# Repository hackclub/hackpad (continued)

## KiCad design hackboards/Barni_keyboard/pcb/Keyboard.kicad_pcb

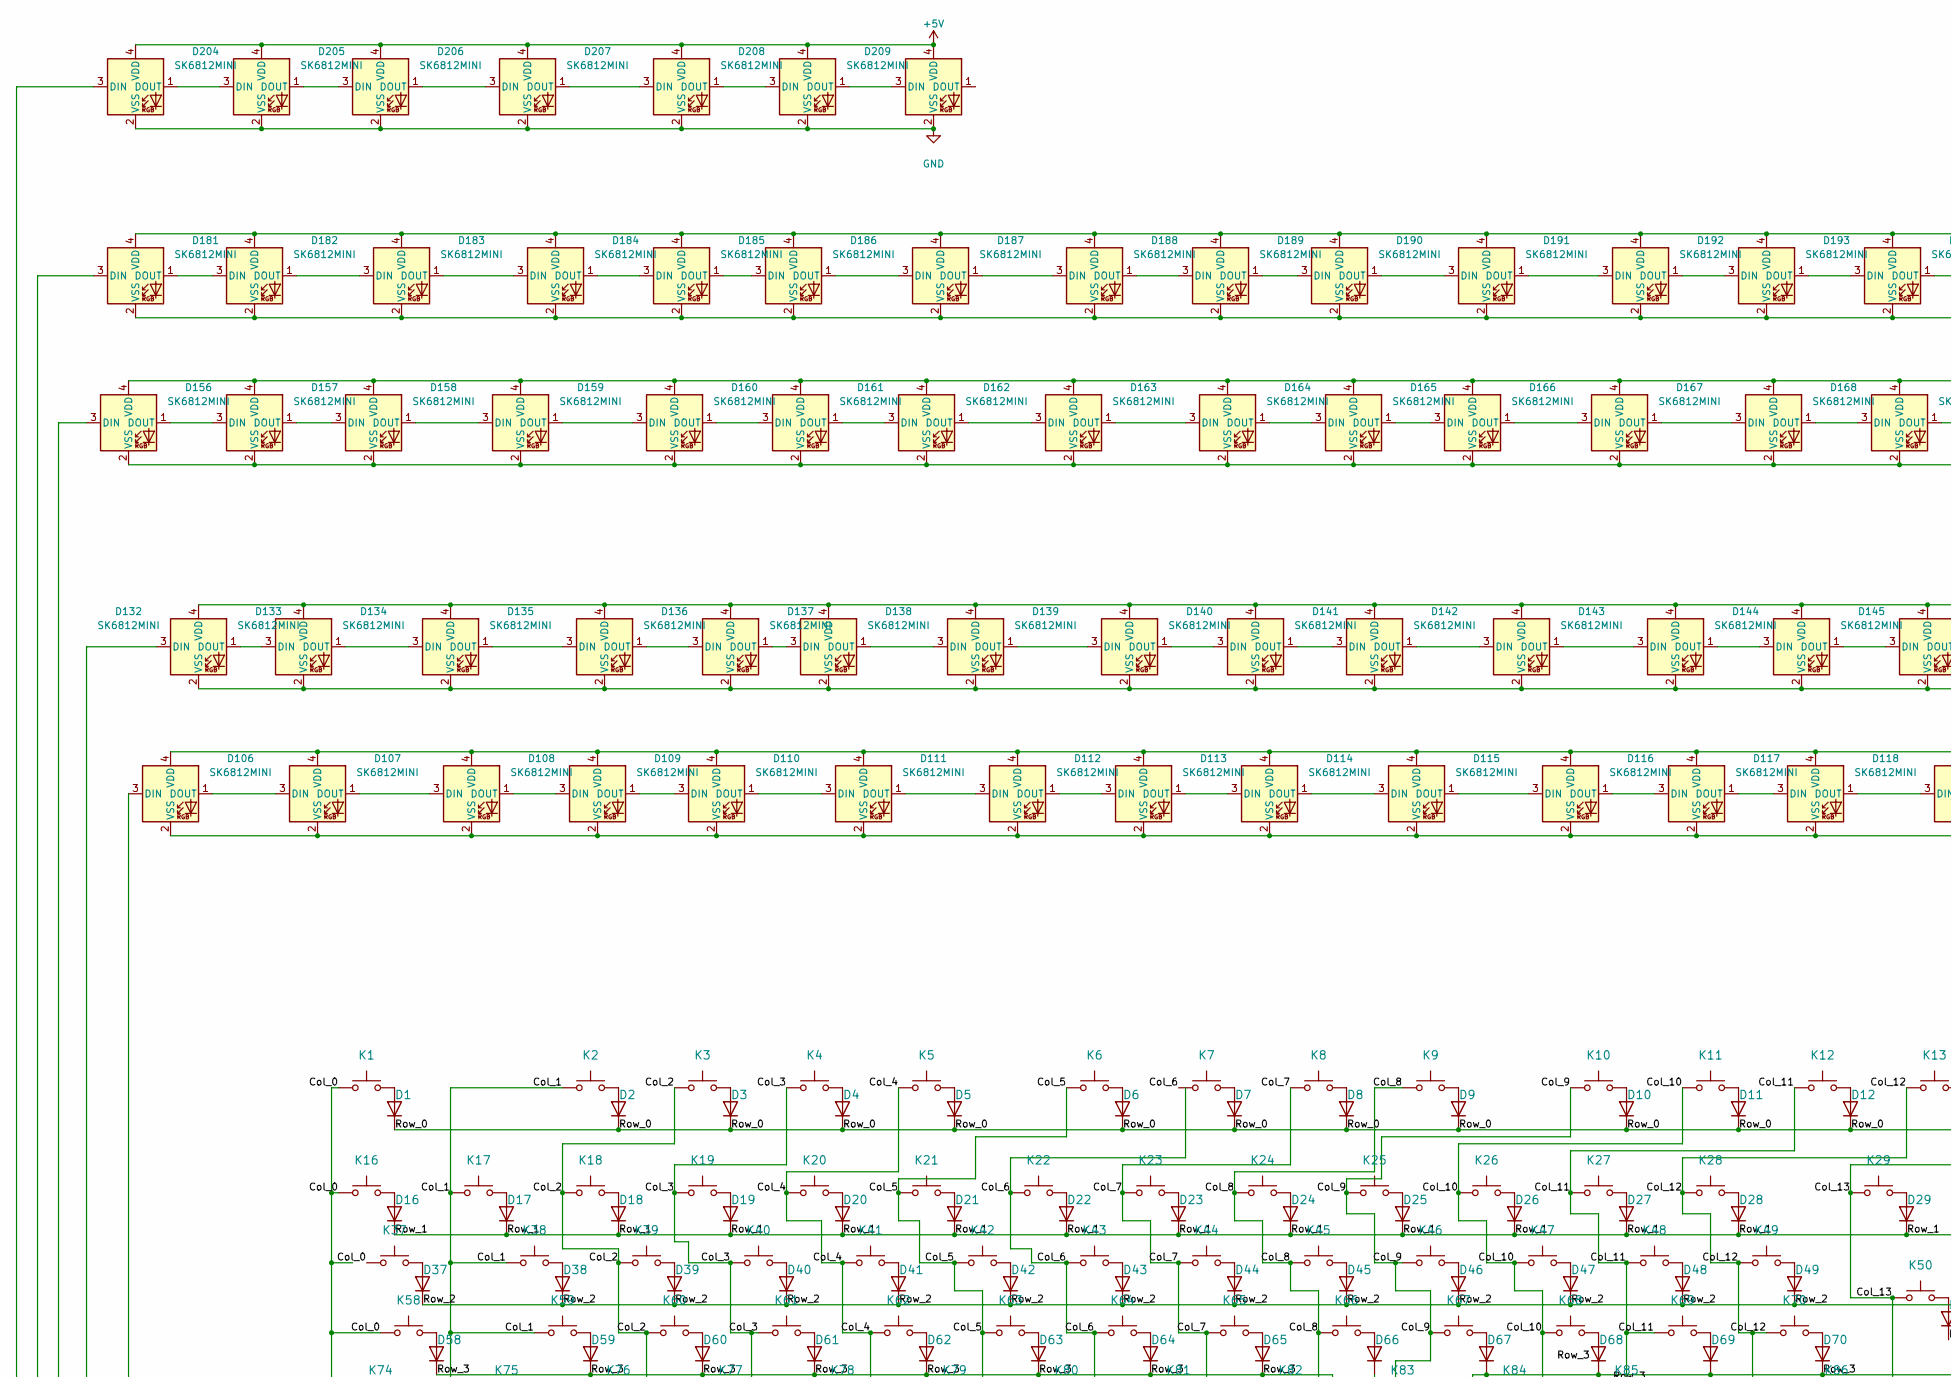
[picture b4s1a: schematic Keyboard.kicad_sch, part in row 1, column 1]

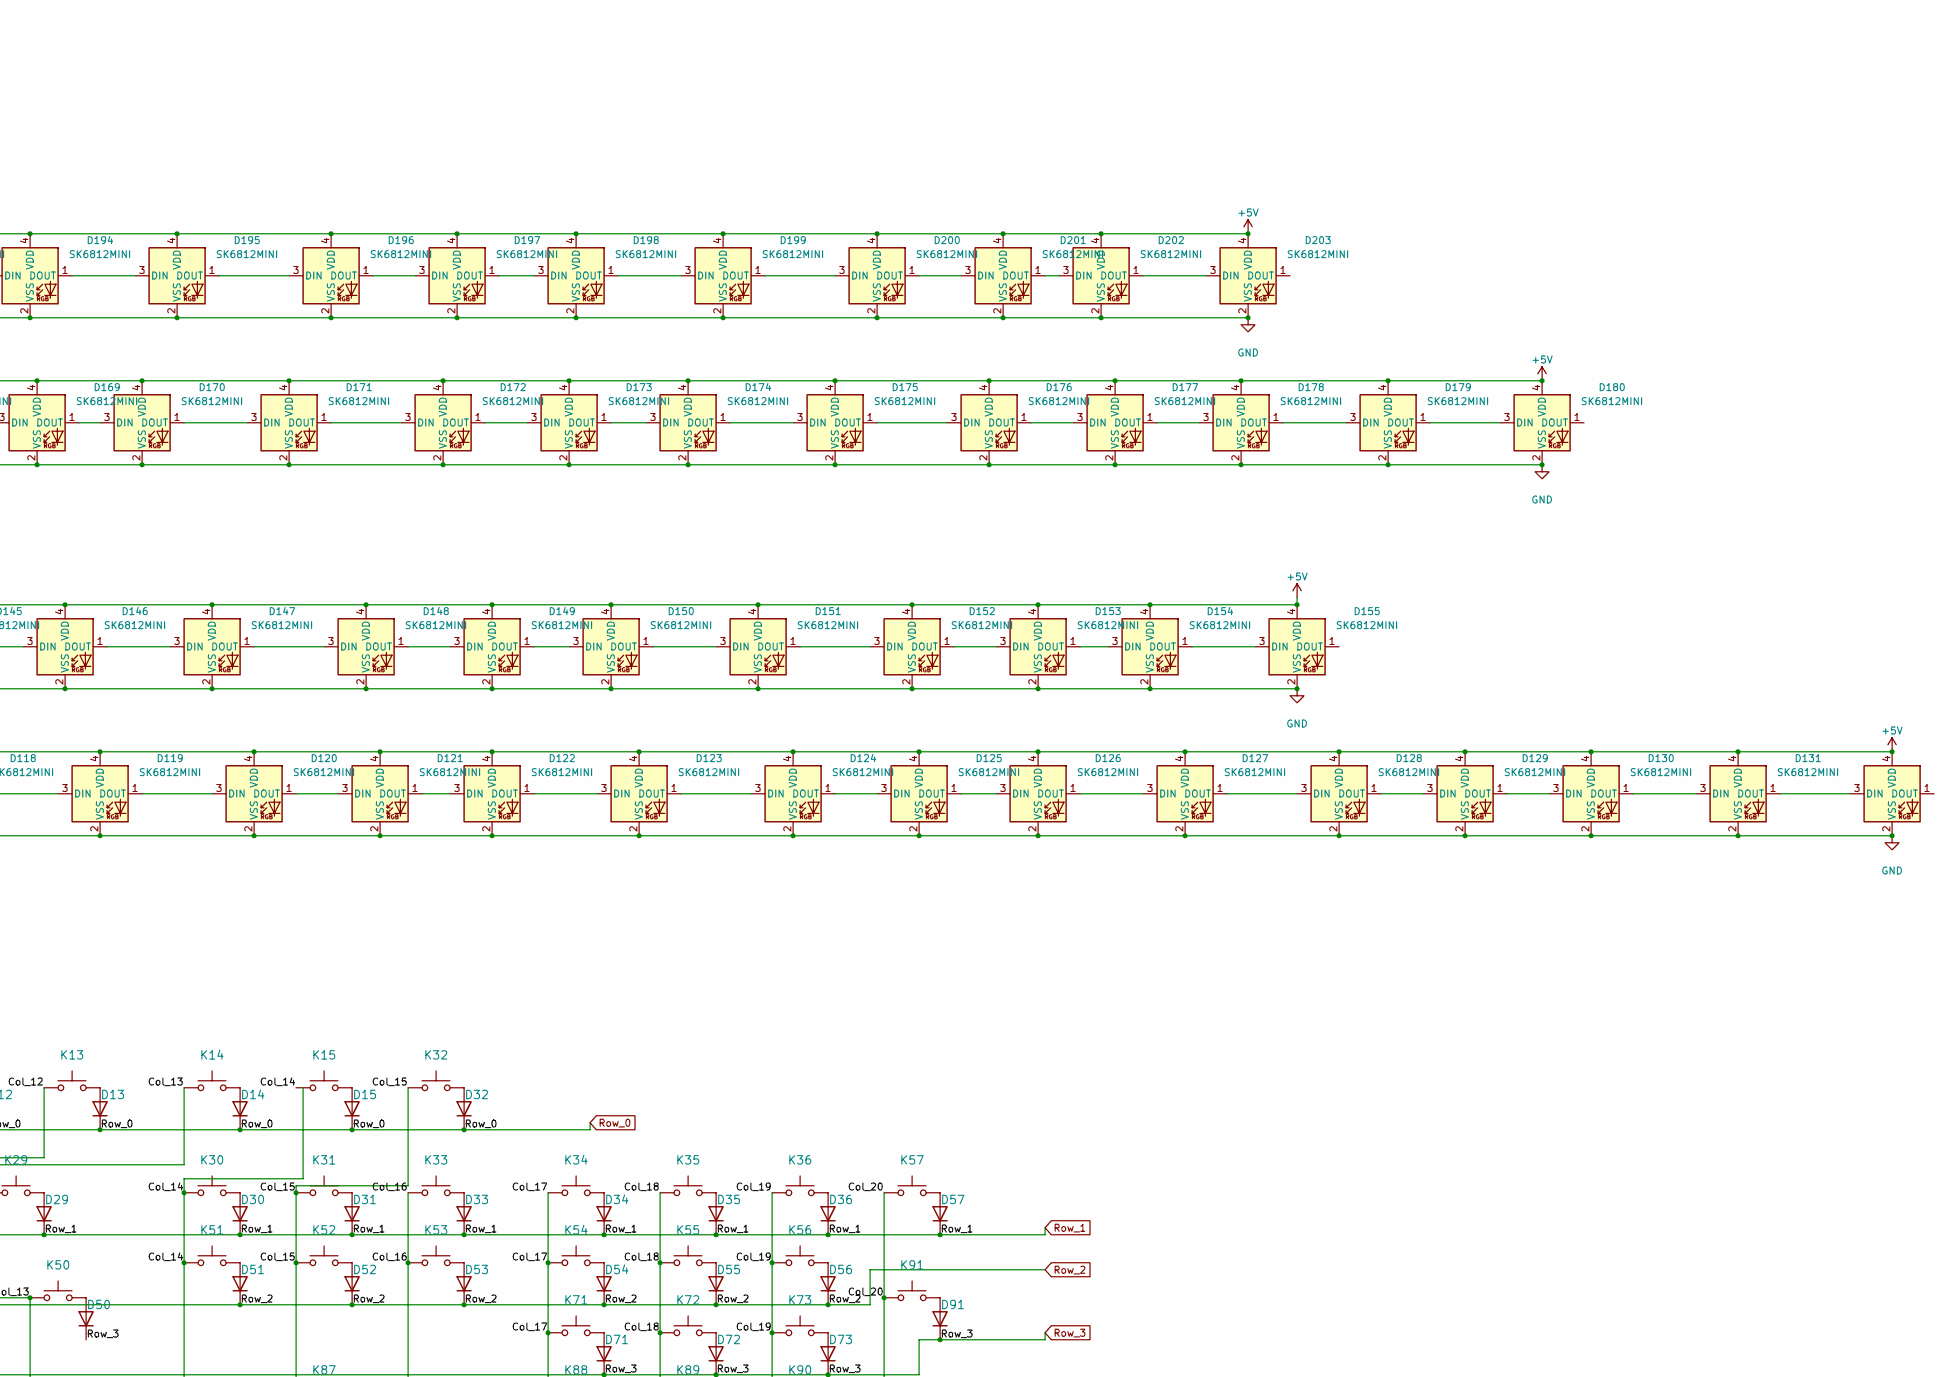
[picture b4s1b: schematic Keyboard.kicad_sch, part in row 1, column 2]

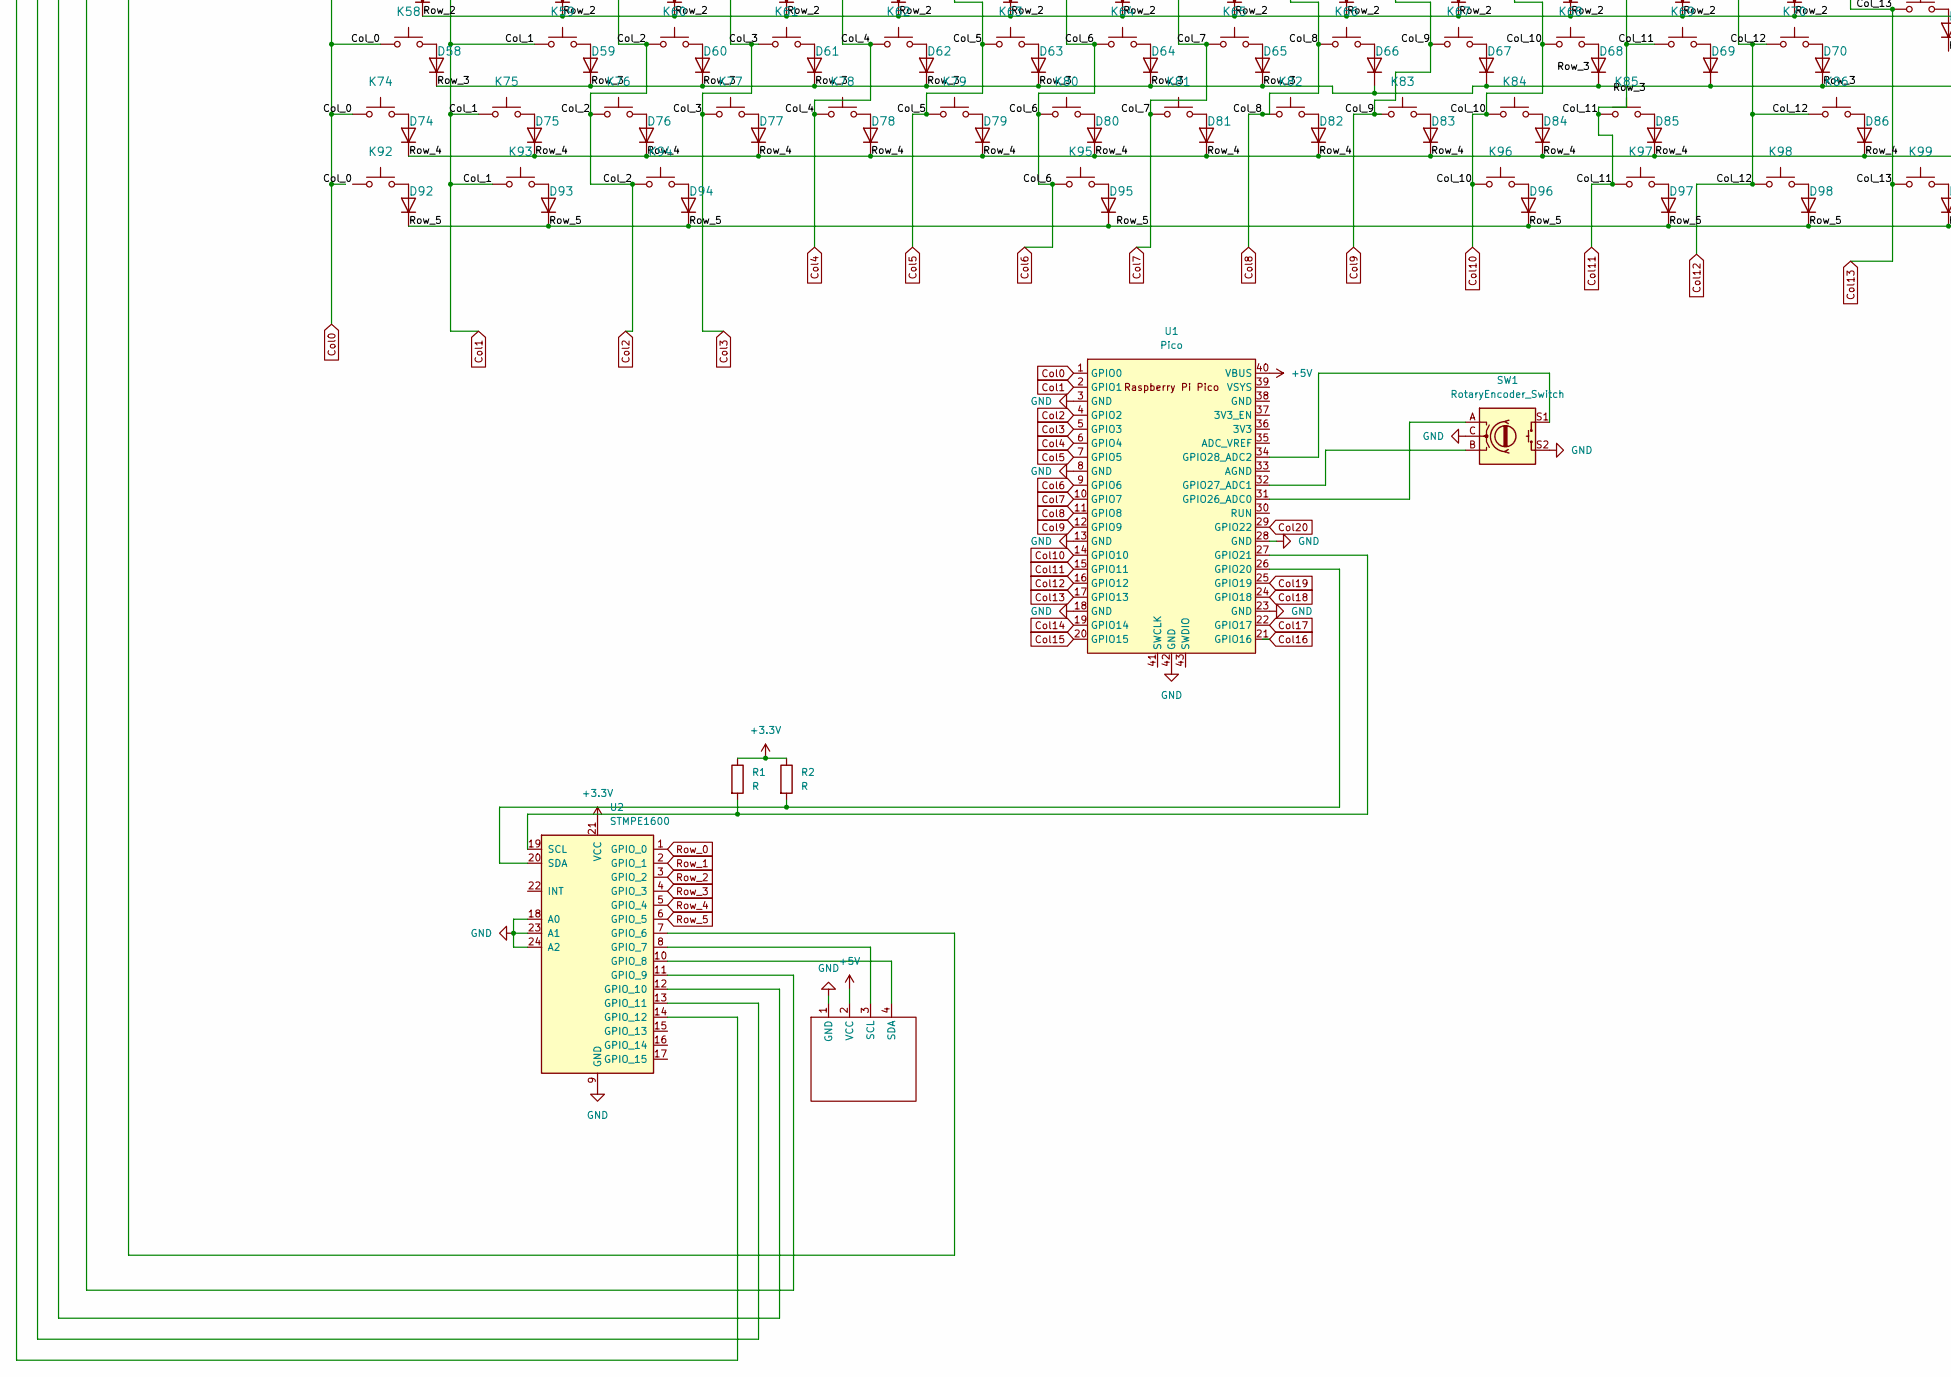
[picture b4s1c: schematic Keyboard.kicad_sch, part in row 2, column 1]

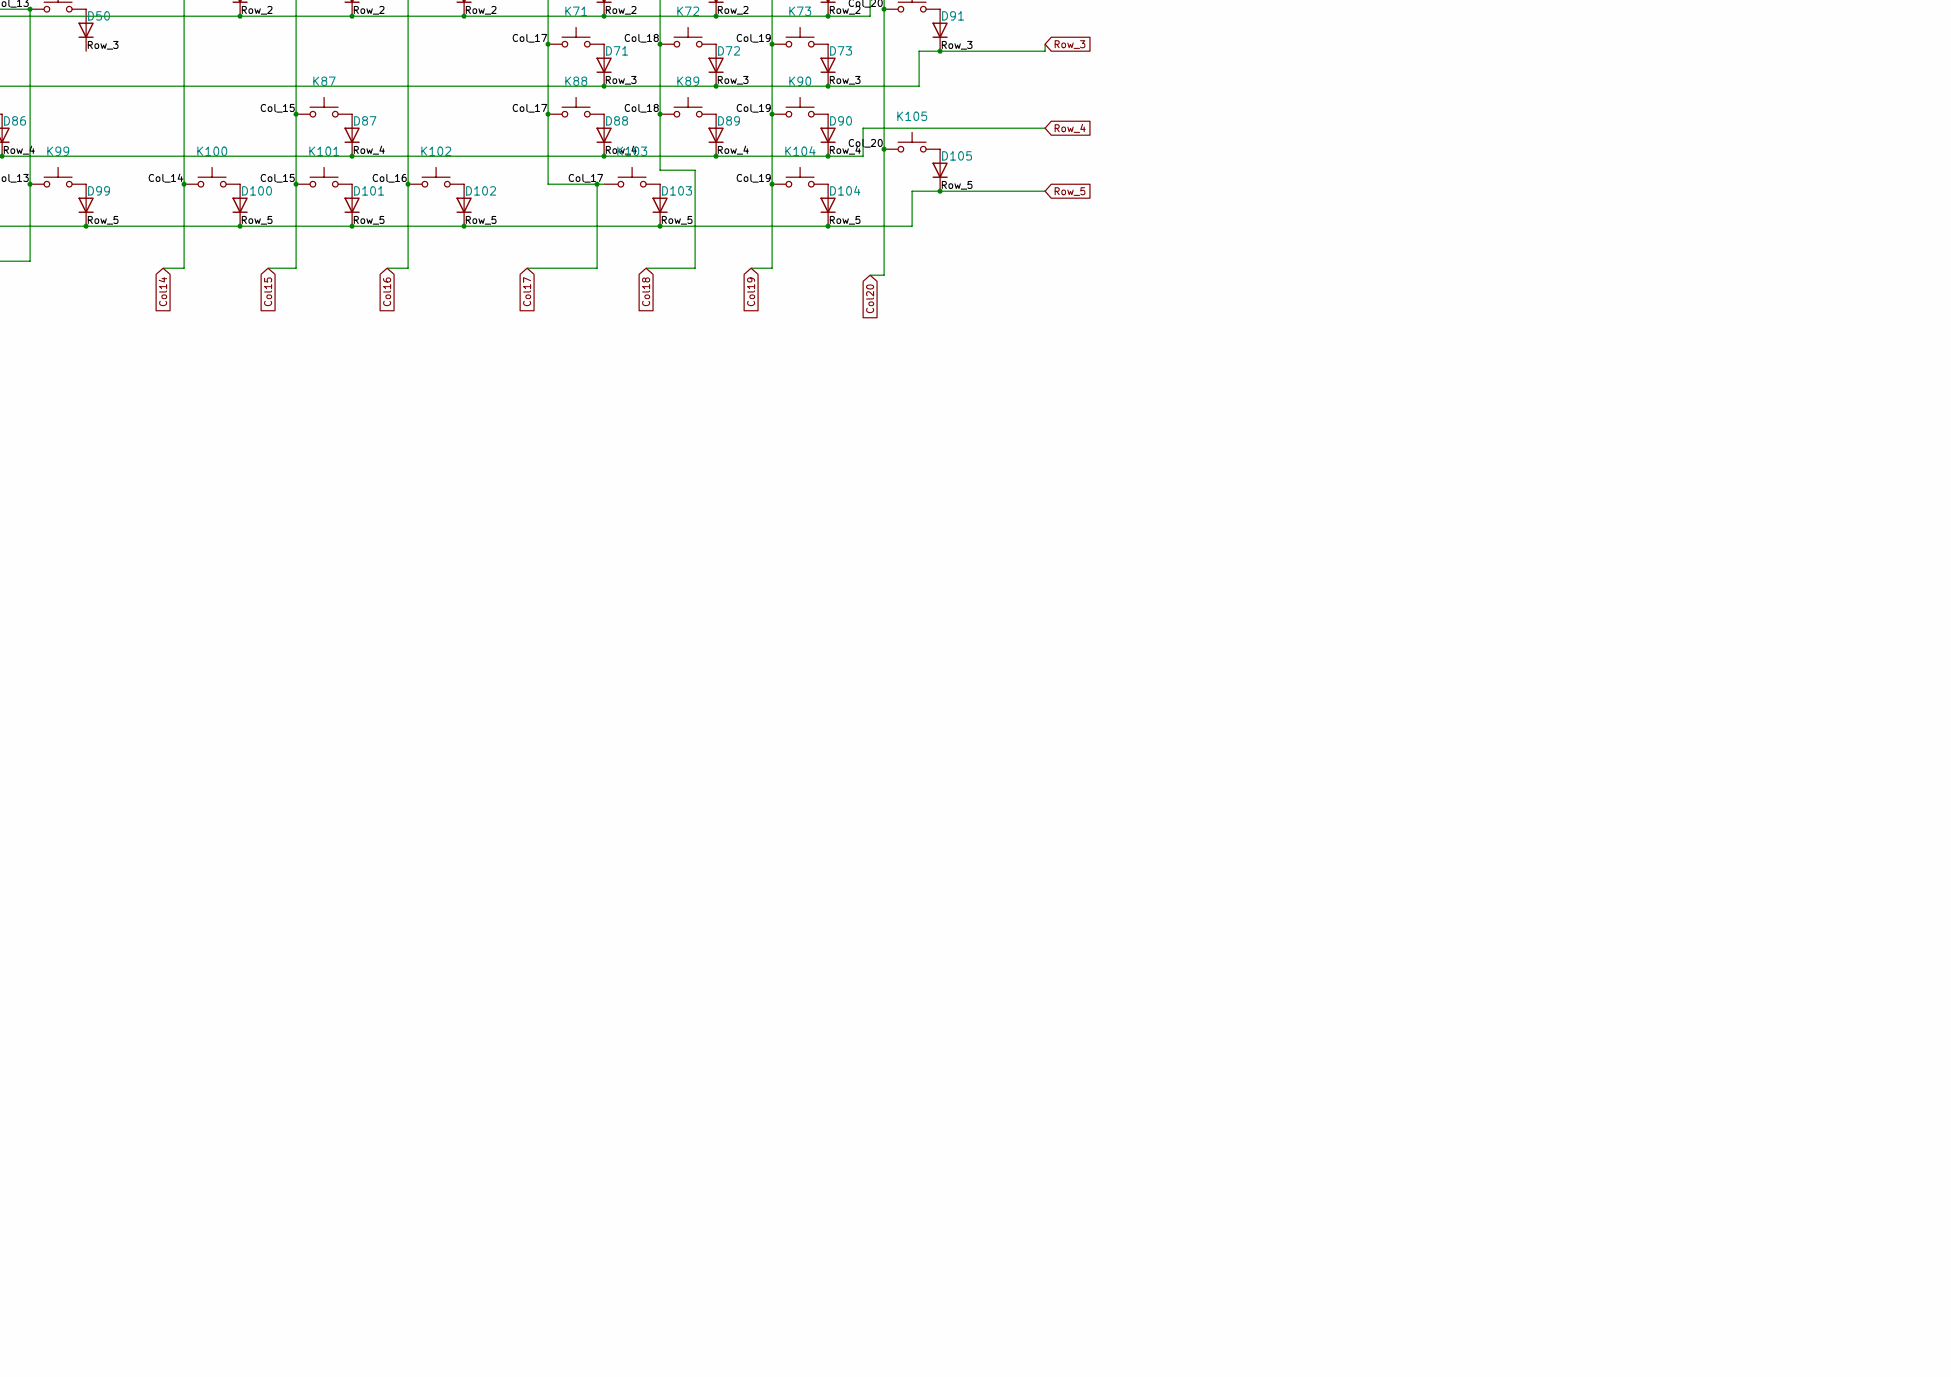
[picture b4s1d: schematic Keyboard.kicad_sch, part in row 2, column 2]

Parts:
D1, D2, D3, D4, D5, D6, D7, D8, D9, D10, D11, D12, D13, D14, D15, D16, D17, D18, D19, D20, D21, D22, D23, D24, D25, D26, D27, D28, D29, D30, D31, D32, D33, D34, D35, D36, D37, D38, D39, D40, D41, D42, D43, D44, D45, D46, D47, D48, D49, D50, D51, D52, D53, D54, D55, D56, D57, D58, D59, D60, D61, D62, D63, D64, D65, D66, D67, D68, D69, D70, D71, D72, D73, D74, D75, D76, D77, D78, D79, D80, D81, D82, D83, D84, D85, D86, D87, D88, D89, D90, D91, D92, D93, D94, D95, D96, D97, D98, D99, D100, D101, D102, D103, D104, D105: D; D_0805_2012Metric_Pad1.15x1.40mm_HandSolder
D106, D107, D108, D109, D110, D111, D112, D113, D114, D115, D116, D117, D118, D119, D120, D121, D122, D123, D124, D125, D126, D127, D128, D129, D130, D131, D132, D133, D134, D135, D136, D137, D138, D139, D140, D141, D142, D143, D144, D145, D146, D147, D148, D149, D150, D151, D152, D153, D154, D155, D156, D157, D158, D159, D160, D161, D162, D163, D164, D165, D166, D167, D168, D169, D170, D171, D172, D173, D174, D175, D176, D177, D178, D179, D180, D181, D182, D183, D184, D185, D186, D187, D188, D189, D190, D191, D192, D193, D194, D195, D196, D197, D198, D199, D200, D201, D202, D203, D204, D205, D206, D207, D208, D209, D210: SK6812MINI; LED_SK6812MINI_PLCC4_3.5x3.5mm_P1.75mm
K1: Esc; SW_Cherry_MX_1.00u_PCB
K2: F1; SW_Cherry_MX_1.00u_PCB
K3: F2; SW_Cherry_MX_1.00u_PCB
K4: F3; SW_Cherry_MX_1.00u_PCB
K5: F4; SW_Cherry_MX_1.00u_PCB
K6: F5; SW_Cherry_MX_1.00u_PCB
K7: F6; SW_Cherry_MX_1.00u_PCB
K8: F7; SW_Cherry_MX_1.00u_PCB
K9: F8; SW_Cherry_MX_1.00u_PCB
K10: F9; SW_Cherry_MX_1.00u_PCB
K11: F10; SW_Cherry_MX_1.00u_PCB
K12: F11; SW_Cherry_MX_1.00u_PCB
K13: F12; SW_Cherry_MX_1.00u_PCB
K14: PrtSc; SW_Cherry_MX_1.00u_PCB
K15: Scroll Lock; SW_Cherry_MX_1.00u_PCB
K16: ¬,`; SW_Cherry_MX_1.00u_PCB
K17: !,1; SW_Cherry_MX_1.00u_PCB
K18: ",2; SW_Cherry_MX_1.00u_PCB
K19: £,3; SW_Cherry_MX_1.00u_PCB
K20: $,4; SW_Cherry_MX_1.00u_PCB
K21: %,5; SW_Cherry_MX_1.00u_PCB
K22: ^,6; SW_Cherry_MX_1.00u_PCB
K23: &,7; SW_Cherry_MX_1.00u_PCB
K24: *,8; SW_Cherry_MX_1.00u_PCB
K25: (,9; SW_Cherry_MX_1.00u_PCB
K26: ),0; SW_Cherry_MX_1.00u_PCB
K27: _,-; SW_Cherry_MX_1.00u_PCB
K28: +,=; SW_Cherry_MX_1.00u_PCB
K29: Backspace; SW_Cherry_MX_2.00u_PCB
K30: Insert; SW_Cherry_MX_1.00u_PCB
K31: Home; SW_Cherry_MX_1.00u_PCB
K32: Pause,Break; SW_Cherry_MX_1.00u_PCB
K33: PgUp; SW_Cherry_MX_1.00u_PCB
K34: Num Lock; SW_Cherry_MX_1.00u_PCB
K35: /; SW_Cherry_MX_1.00u_PCB
K36: *; SW_Cherry_MX_1.00u_PCB
K37: Tab; SW_Cherry_MX_1.50u_PCB
K38: Q; SW_Cherry_MX_1.00u_PCB
K39: W; SW_Cherry_MX_1.00u_PCB
K40: E; SW_Cherry_MX_1.00u_PCB
K41: R; SW_Cherry_MX_1.00u_PCB
K42: T; SW_Cherry_MX_1.00u_PCB
K43: Y; SW_Cherry_MX_1.00u_PCB
K44: U; SW_Cherry_MX_1.00u_PCB
K45: I; SW_Cherry_MX_1.00u_PCB
K46: O; SW_Cherry_MX_1.00u_PCB
K47: P; SW_Cherry_MX_1.00u_PCB
K48: {,[; SW_Cherry_MX_1.00u_PCB
K49: },]; SW_Cherry_MX_1.00u_PCB
K50: Enter; SW_Cherry_MX_1.25u_PCB
K51: Delete; SW_Cherry_MX_1.00u_PCB
K52: End; SW_Cherry_MX_1.00u_PCB
K53: PgDn; SW_Cherry_MX_1.00u_PCB
K54: 7,Home; SW_Cherry_MX_1.00u_PCB
K55: 8,↑; SW_Cherry_MX_1.00u_PCB
K56: 9,PgUp; SW_Cherry_MX_1.00u_PCB
K57: -; SW_Cherry_MX_1.00u_PCB
K58: Caps Lock; SW_Cherry_MX_1.75u_PCB
K59: A; SW_Cherry_MX_1.00u_PCB
K60: S; SW_Cherry_MX_1.00u_PCB
K61: D; SW_Cherry_MX_1.00u_PCB
K62: F; SW_Cherry_MX_1.00u_PCB
K63: G; SW_Cherry_MX_1.00u_PCB
K64: H; SW_Cherry_MX_1.00u_PCB
K65: J; SW_Cherry_MX_1.00u_PCB
K66: K; SW_Cherry_MX_1.00u_PCB
K67: L; SW_Cherry_MX_1.00u_PCB
K68: :,;; SW_Cherry_MX_1.00u_PCB
K69: @,'; SW_Cherry_MX_1.00u_PCB
K70: ~~,#; SW_Cherry_MX_1.00u_PCB
K71: 4,←; SW_Cherry_MX_1.00u_PCB
K72: 5; SW_Cherry_MX_1.00u_PCB
K73: 6,→; SW_Cherry_MX_1.00u_PCB
K74: Shift; SW_Cherry_MX_1.25u_PCB
K75: |,\; SW_Cherry_MX_1.00u_PCB
K76: Z; SW_Cherry_MX_1.00u_PCB
K77: X; SW_Cherry_MX_1.00u_PCB
K78: C; SW_Cherry_MX_1.00u_PCB
K79: V; SW_Cherry_MX_1.00u_PCB
K80: B; SW_Cherry_MX_1.00u_PCB
K81: N; SW_Cherry_MX_1.00u_PCB
K82: M; SW_Cherry_MX_1.00u_PCB
K83: <,,; SW_Cherry_MX_1.00u_PCB
K84: >,.; SW_Cherry_MX_1.00u_PCB
K85: ?,/; SW_Cherry_MX_1.00u_PCB
K86: Shift; SW_Cherry_MX_2.75u_PCB
K87: ↑; SW_Cherry_MX_1.00u_PCB
K88: 1,End; SW_Cherry_MX_1.00u_PCB
K89: 2,↓; SW_Cherry_MX_1.00u_PCB
K90: 3,PgDn; SW_Cherry_MX_1.00u_PCB
K91: +; SW_Cherry_MX_1.00u_PCB
K92, K99: Ctrl; SW_Cherry_MX_1.25u_PCB
K93, K97: Win; SW_Cherry_MX_1.25u_PCB
K94: Alt; SW_Cherry_MX_1.25u_PCB
K95: Blank; SW_Cherry_MX_6.25u_PCB
K96: AltGr; SW_Cherry_MX_1.25u_PCB
K98: Menu; SW_Cherry_MX_1.25u_PCB
K100: ←; SW_Cherry_MX_1.00u_PCB
K101: ↓; SW_Cherry_MX_1.00u_PCB
K102: →; SW_Cherry_MX_1.00u_PCB
K103: 0,Ins; SW_Cherry_MX_2.00u_PCB
K104: .,Del; SW_Cherry_MX_1.00u_PCB
K105: Enter; SW_Cherry_MX_1.00u_PCB
R1, R2: R; R_Axial_DIN0204_L3.6mm_D1.6mm_P7.62mm_Horizontal
SW1: RotaryEncoder_Switch; RotaryEncoder_Alps_EC11E-Switch_Vertical_H20mm
U1: Pico; RPi_Pico_SMD_TH
U2: STMPE1600; 16-bit IO Expander
U3: (no value)

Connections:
+3.3V: R1.1, R2.1, U2.21 (VCC)
+5V: D106.4 (VDD), D107.4 (VDD), D108.4 (VDD), D109.4 (VDD), D110.4 (VDD), D111.4 (VDD), D112.4 (VDD), D113.4 (VDD), D114.4 (VDD), D115.4 (VDD), D116.4 (VDD), D117.4 (VDD), D118.4 (VDD), D119.4 (VDD), D120.4 (VDD), D121.4 (VDD), D122.4 (VDD), D123.4 (VDD), D124.4 (VDD), D125.4 (VDD), D126.4 (VDD), D127.4 (VDD), D128.4 (VDD), D129.4 (VDD), D130.4 (VDD), D131.4 (VDD), D132.4 (VDD), D133.4 (VDD), D134.4 (VDD), D135.4 (VDD), D136.4 (VDD), D137.4 (VDD), D138.4 (VDD), D139.4 (VDD), D140.4 (VDD), D141.4 (VDD), D142.4 (VDD), D143.4 (VDD), D144.4 (VDD), D145.4 (VDD), D146.4 (VDD), D147.4 (VDD), D148.4 (VDD), D149.4 (VDD), D150.4 (VDD), D151.4 (VDD), D152.4 (VDD), D153.4 (VDD), D154.4 (VDD), D155.4 (VDD), D156.4 (VDD), D157.4 (VDD), D158.4 (VDD), D159.4 (VDD), D160.4 (VDD), D161.4 (VDD), D162.4 (VDD), D163.4 (VDD), D164.4 (VDD), D165.4 (VDD), D166.4 (VDD), D167.4 (VDD), D168.4 (VDD), D169.4 (VDD), D170.4 (VDD), D171.4 (VDD), D172.4 (VDD), D173.4 (VDD), D174.4 (VDD), D175.4 (VDD), D176.4 (VDD), D177.4 (VDD), D178.4 (VDD), D179.4 (VDD), D180.4 (VDD), D181.4 (VDD), D182.4 (VDD), D183.4 (VDD), D184.4 (VDD), D185.4 (VDD), D186.4 (VDD), D187.4 (VDD), D188.4 (VDD), D189.4 (VDD), D190.4 (VDD), D191.4 (VDD), D192.4 (VDD), D193.4 (VDD), D194.4 (VDD), D195.4 (VDD), D196.4 (VDD), D197.4 (VDD), D198.4 (VDD), D199.4 (VDD), D200.4 (VDD), D201.4 (VDD), D202.4 (VDD), D203.4 (VDD), D204.4 (VDD), D205.4 (VDD), D206.4 (VDD), D207.4 (VDD), D208.4 (VDD), D209.4 (VDD), D210.4 (VDD), U1.40 (VBUS), U3.2 (VCC)
Col0: K1.1, K16.1, K37.1, K58.1, K74.1, K92.1, U1.1 (GPIO0)
Col1: K2.1, K17.1, K38.1, K59.1, K75.1, K93.1, U1.2 (GPIO1)
Col2: K3.1, K18.1, K39.1, K60.1, K76.1, K94.1, U1.4 (GPIO2)
Col3: K4.1, K19.1, K40.1, K61.1, K77.1, U1.5 (GPIO3)
Col4: K5.1, K20.1, K41.1, K62.1, K78.1, U1.6 (GPIO4)
Col5: K6.1, K21.1, K42.1, K63.1, K79.1, U1.7 (GPIO5)
Col6: K7.1, K22.1, K43.1, K64.1, K80.1, K95.1, U1.9 (GPIO6)
Col7: K8.1, K23.1, K44.1, K65.1, K81.1, U1.10 (GPIO7)
Col8: K9.1, K24.1, K45.1, K66.1, K82.1, U1.11 (GPIO8)
Col9: K10.1, K25.1, K46.1, K67.1, K83.1, U1.12 (GPIO9)
Col10: K11.1, K26.1, K47.1, K68.1, K84.1, K96.1, U1.14 (GPIO10)
Col11: K12.1, K27.1, K48.1, K69.1, K85.1, K97.1, U1.15 (GPIO11)
Col12: K13.1, K28.1, K49.1, K70.1, K86.1, K98.1, U1.16 (GPIO12)
Col13: K14.1, K29.1, K50.1, K99.1, U1.17 (GPIO13)
Col14: K15.1, K30.1, K51.1, K100.1, U1.19 (GPIO14)
Col15: K31.1, K32.1, K52.1, K87.1, K101.1, U1.20 (GPIO15)
Col16: K33.1, K53.1, K102.1, U1.21 (GPIO16)
Col17: K34.1, K54.1, K71.1, K88.1, K103.1, U1.22 (GPIO17)
Col18: K35.1, K55.1, K72.1, K89.1, U1.24 (GPIO18)
Col19: K36.1, K56.1, K73.1, K90.1, K104.1, U1.25 (GPIO19)
Col20: K57.1, K91.1, K105.1, U1.29 (GPIO22)
GND: D106.2 (VSS), D107.2 (VSS), D108.2 (VSS), D109.2 (VSS), D110.2 (VSS), D111.2 (VSS), D112.2 (VSS), D113.2 (VSS), D114.2 (VSS), D115.2 (VSS), D116.2 (VSS), D117.2 (VSS), D118.2 (VSS), D119.2 (VSS), D120.2 (VSS), D121.2 (VSS), D122.2 (VSS), D123.2 (VSS), D124.2 (VSS), D125.2 (VSS), D126.2 (VSS), D127.2 (VSS), D128.2 (VSS), D129.2 (VSS), D130.2 (VSS), D131.2 (VSS), D132.2 (VSS), D133.2 (VSS), D134.2 (VSS), D135.2 (VSS), D136.2 (VSS), D137.2 (VSS), D138.2 (VSS), D139.2 (VSS), D140.2 (VSS), D141.2 (VSS), D142.2 (VSS), D143.2 (VSS), D144.2 (VSS), D145.2 (VSS), D146.2 (VSS), D147.2 (VSS), D148.2 (VSS), D149.2 (VSS), D150.2 (VSS), D151.2 (VSS), D152.2 (VSS), D153.2 (VSS), D154.2 (VSS), D155.2 (VSS), D156.2 (VSS), D157.2 (VSS), D158.2 (VSS), D159.2 (VSS), D160.2 (VSS), D161.2 (VSS), D162.2 (VSS), D163.2 (VSS), D164.2 (VSS), D165.2 (VSS), D166.2 (VSS), D167.2 (VSS), D168.2 (VSS), D169.2 (VSS), D170.2 (VSS), D171.2 (VSS), D172.2 (VSS), D173.2 (VSS), D174.2 (VSS), D175.2 (VSS), D176.2 (VSS), D177.2 (VSS), D178.2 (VSS), D179.2 (VSS), D180.2 (VSS), D181.2 (VSS), D182.2 (VSS), D183.2 (VSS), D184.2 (VSS), D185.2 (VSS), D186.2 (VSS), D187.2 (VSS), D188.2 (VSS), D189.2 (VSS), D190.2 (VSS), D191.2 (VSS), D192.2 (VSS), D193.2 (VSS), D194.2 (VSS), D195.2 (VSS), D196.2 (VSS), D197.2 (VSS), D198.2 (VSS), D199.2 (VSS), D200.2 (VSS), D201.2 (VSS), D202.2 (VSS), D203.2 (VSS), D204.2 (VSS), D205.2 (VSS), D206.2 (VSS), D207.2 (VSS), D208.2 (VSS), D209.2 (VSS), D210.2 (VSS), SW1.C, SW1.S2, U1.3 (GND), U1.8 (GND), U1.13 (GND), U1.18 (GND), U1.23 (GND), U1.28 (GND), U1.42 (GND), U2.9 (GND), U2.18 (A0), U2.23 (A1), U2.24 (A2), U3.1 (GND)
unnamed: D1.2 (A), K1.2
unnamed: D2.2 (A), K2.2
unnamed: D3.2 (A), K3.2
unnamed: D4.2 (A), K4.2
unnamed: D5.2 (A), K5.2
unnamed: D6.2 (A), K6.2
unnamed: D7.2 (A), K7.2
unnamed: D8.2 (A), K8.2
unnamed: D9.2 (A), K9.2
unnamed: D10.2 (A), K10.2
unnamed: D11.2 (A), K11.2
unnamed: D12.2 (A), K12.2
unnamed: D13.2 (A), K13.2
unnamed: D14.2 (A), K14.2
unnamed: D15.2 (A), K15.2
unnamed: D16.2 (A), K16.2
unnamed: D17.2 (A), K17.2
unnamed: D18.2 (A), K18.2
unnamed: D19.2 (A), K19.2
unnamed: D20.2 (A), K20.2
unnamed: D21.2 (A), K21.2
unnamed: D22.2 (A), K22.2
unnamed: D23.2 (A), K23.2
unnamed: D24.2 (A), K24.2
unnamed: D25.2 (A), K25.2
unnamed: D26.2 (A), K26.2
unnamed: D27.2 (A), K27.2
unnamed: D28.2 (A), K28.2
unnamed: D29.2 (A), K29.2
unnamed: D30.2 (A), K30.2
unnamed: D31.2 (A), K31.2
unnamed: D32.2 (A), K32.2
unnamed: D33.2 (A), K33.2
unnamed: D34.2 (A), K34.2
unnamed: D35.2 (A), K35.2
unnamed: D36.2 (A), K36.2
unnamed: D37.2 (A), K37.2
unnamed: D38.2 (A), K38.2
unnamed: D39.2 (A), K39.2
unnamed: D40.2 (A), K40.2
unnamed: D41.2 (A), K41.2
unnamed: D42.2 (A), K42.2
unnamed: D43.2 (A), K43.2
unnamed: D44.2 (A), K44.2
unnamed: D45.2 (A), K45.2
unnamed: D46.2 (A), K46.2
unnamed: D47.2 (A), K47.2
unnamed: D48.2 (A), K48.2
unnamed: D49.2 (A), K49.2
unnamed: D50.2 (A), K50.2
unnamed: D51.2 (A), K51.2
unnamed: D52.2 (A), K52.2
unnamed: D53.2 (A), K53.2
unnamed: D54.2 (A), K54.2
unnamed: D55.2 (A), K55.2
unnamed: D56.2 (A), K56.2
unnamed: D57.2 (A), K57.2
unnamed: D58.2 (A), K58.2
unnamed: D59.2 (A), K59.2
unnamed: D60.2 (A), K60.2
unnamed: D61.2 (A), K61.2
unnamed: D62.2 (A), K62.2
unnamed: D63.2 (A), K63.2
unnamed: D64.2 (A), K64.2
unnamed: D65.2 (A), K65.2
unnamed: D66.2 (A), K66.2
unnamed: D67.2 (A), K67.2
unnamed: D68.2 (A), K68.2
unnamed: D69.2 (A), K69.2
unnamed: D70.2 (A), K70.2
unnamed: D71.2 (A), K71.2
unnamed: D72.2 (A), K72.2
unnamed: D73.2 (A), K73.2
unnamed: D74.2 (A), K74.2
unnamed: D75.2 (A), K75.2
unnamed: D76.2 (A), K76.2
unnamed: D77.2 (A), K77.2
unnamed: D78.2 (A), K78.2
unnamed: D79.2 (A), K79.2
unnamed: D80.2 (A), K80.2
unnamed: D81.2 (A), K81.2
unnamed: D82.2 (A), K82.2
unnamed: D83.2 (A), K83.2
unnamed: D84.2 (A), K84.2
unnamed: D85.2 (A), K85.2
unnamed: D86.2 (A), K86.2
unnamed: D87.2 (A), K87.2
unnamed: D88.2 (A), K88.2
unnamed: D89.2 (A), K89.2
unnamed: D90.2 (A), K90.2
unnamed: D91.2 (A), K91.2
unnamed: D92.2 (A), K92.2
unnamed: D93.2 (A), K93.2
unnamed: D94.2 (A), K94.2
unnamed: D95.2 (A), K95.2
unnamed: D96.2 (A), K96.2
unnamed: D97.2 (A), K97.2
unnamed: D98.2 (A), K98.2
unnamed: D99.2 (A), K99.2
unnamed: D100.2 (A), K100.2
unnamed: D101.2 (A), K101.2
unnamed: D102.2 (A), K102.2
unnamed: D103.2 (A), K103.2
unnamed: D104.2 (A), K104.2
unnamed: D105.2 (A), K105.2
unnamed: D106.3 (DIN), U2.7 (GPIO_6)
unnamed: D106.1 (DOUT), D107.3 (DIN)
unnamed: D107.1 (DOUT), D108.3 (DIN)
unnamed: D108.1 (DOUT), D109.3 (DIN)
unnamed: D109.1 (DOUT), D110.3 (DIN)
unnamed: D110.1 (DOUT), D111.3 (DIN)
unnamed: D111.1 (DOUT), D112.3 (DIN)
unnamed: D112.1 (DOUT), D113.3 (DIN)
unnamed: D113.1 (DOUT), D114.3 (DIN)
unnamed: D114.1 (DOUT), D115.3 (DIN)
unnamed: D115.1 (DOUT), D116.3 (DIN)
unnamed: D116.1 (DOUT), D117.3 (DIN)
unnamed: D117.1 (DOUT), D118.3 (DIN)
unnamed: D118.1 (DOUT), D119.3 (DIN)
unnamed: D119.1 (DOUT), D120.3 (DIN)
unnamed: D120.1 (DOUT), D121.3 (DIN)
unnamed: D121.1 (DOUT), D122.3 (DIN)
unnamed: D122.1 (DOUT), D123.3 (DIN)
unnamed: D123.1 (DOUT), D124.3 (DIN)
unnamed: D124.1 (DOUT), D125.3 (DIN)
unnamed: D125.1 (DOUT), D126.3 (DIN)
unnamed: D126.1 (DOUT), D127.3 (DIN)
unnamed: D127.1 (DOUT), D128.3 (DIN)
unnamed: D128.1 (DOUT), D129.3 (DIN)
unnamed: D129.1 (DOUT), D130.3 (DIN)
unnamed: D130.1 (DOUT), D131.3 (DIN)
unnamed: D131.1 (DOUT), D132.3 (DIN)
unnamed: D133.3 (DIN), U2.11 (GPIO_9)
unnamed: D133.1 (DOUT), D134.3 (DIN)
unnamed: D134.1 (DOUT), D135.3 (DIN)
unnamed: D135.1 (DOUT), D136.3 (DIN)
unnamed: D136.1 (DOUT), D137.3 (DIN)
unnamed: D137.1 (DOUT), D138.3 (DIN)
unnamed: D138.1 (DOUT), D139.3 (DIN)
unnamed: D139.1 (DOUT), D140.3 (DIN)
unnamed: D140.1 (DOUT), D141.3 (DIN)
unnamed: D141.1 (DOUT), D142.3 (DIN)
unnamed: D142.1 (DOUT), D143.3 (DIN)
unnamed: D143.1 (DOUT), D144.3 (DIN)
unnamed: D144.1 (DOUT), D145.3 (DIN)
unnamed: D145.1 (DOUT), D146.3 (DIN)
unnamed: D146.1 (DOUT), D147.3 (DIN)
unnamed: D147.1 (DOUT), D148.3 (DIN)
unnamed: D148.1 (DOUT), D149.3 (DIN)
unnamed: D149.1 (DOUT), D150.3 (DIN)
unnamed: D150.1 (DOUT), D151.3 (DIN)
unnamed: D151.1 (DOUT), D152.3 (DIN)
unnamed: D152.1 (DOUT), D153.3 (DIN)
unnamed: D153.1 (DOUT), D154.3 (DIN)
unnamed: D154.1 (DOUT), D155.3 (DIN)
unnamed: D156.3 (DIN), U2.12 (GPIO_10)
unnamed: D156.1 (DOUT), D157.3 (DIN)
unnamed: D157.1 (DOUT), D158.3 (DIN)
unnamed: D158.1 (DOUT), D159.3 (DIN)
unnamed: D159.1 (DOUT), D160.3 (DIN)
unnamed: D160.1 (DOUT), D161.3 (DIN)
unnamed: D161.1 (DOUT), D162.3 (DIN)
unnamed: D162.1 (DOUT), D163.3 (DIN)
unnamed: D163.1 (DOUT), D164.3 (DIN)
unnamed: D164.1 (DOUT), D165.3 (DIN)
unnamed: D165.1 (DOUT), D166.3 (DIN)
unnamed: D166.1 (DOUT), D167.3 (DIN)
unnamed: D167.1 (DOUT), D168.3 (DIN)
unnamed: D168.1 (DOUT), D169.3 (DIN)
unnamed: D169.1 (DOUT), D170.3 (DIN)
unnamed: D170.1 (DOUT), D171.3 (DIN)
unnamed: D171.1 (DOUT), D172.3 (DIN)
unnamed: D172.1 (DOUT), D173.3 (DIN)
unnamed: D173.1 (DOUT), D174.3 (DIN)
unnamed: D174.1 (DOUT), D175.3 (DIN)
unnamed: D175.1 (DOUT), D176.3 (DIN)
unnamed: D176.1 (DOUT), D177.3 (DIN)
unnamed: D177.1 (DOUT), D178.3 (DIN)
unnamed: D178.1 (DOUT), D179.3 (DIN)
unnamed: D179.1 (DOUT), D180.3 (DIN)
unnamed: D181.3 (DIN), U2.13 (GPIO_11)
unnamed: D181.1 (DOUT), D182.3 (DIN)
unnamed: D182.1 (DOUT), D183.3 (DIN)
unnamed: D183.1 (DOUT), D184.3 (DIN)
unnamed: D184.1 (DOUT), D185.3 (DIN)
unnamed: D185.1 (DOUT), D186.3 (DIN)
unnamed: D186.1 (DOUT), D187.3 (DIN)
unnamed: D187.1 (DOUT), D188.3 (DIN)
unnamed: D188.1 (DOUT), D189.3 (DIN)
unnamed: D189.1 (DOUT), D190.3 (DIN)
unnamed: D190.1 (DOUT), D191.3 (DIN)
unnamed: D191.1 (DOUT), D192.3 (DIN)
unnamed: D192.1 (DOUT), D193.3 (DIN)
unnamed: D193.1 (DOUT), D194.3 (DIN)
unnamed: D194.1 (DOUT), D195.3 (DIN)
unnamed: D195.1 (DOUT), D196.3 (DIN)
unnamed: D196.1 (DOUT), D197.3 (DIN)
unnamed: D197.1 (DOUT), D198.3 (DIN)
unnamed: D198.1 (DOUT), D199.3 (DIN)
unnamed: D199.1 (DOUT), D200.3 (DIN)
unnamed: D200.1 (DOUT), D201.3 (DIN)
unnamed: D201.1 (DOUT), D202.3 (DIN)
unnamed: D202.1 (DOUT), D203.3 (DIN)
unnamed: D204.3 (DIN), U2.14 (GPIO_12)
unnamed: D204.1 (DOUT), D205.3 (DIN)
unnamed: D205.1 (DOUT), D206.3 (DIN)
unnamed: D206.1 (DOUT), D207.3 (DIN)
unnamed: D207.1 (DOUT), D208.3 (DIN)
unnamed: D208.1 (DOUT), D209.3 (DIN)
unnamed: D209.1 (DOUT), D210.3 (DIN)
unnamed: R2.2, U1.26 (GPIO20), U2.20 (SDA)
unnamed: R1.2, U1.27 (GPIO21), U2.19 (SCL)
unnamed: SW1.A, U1.31 (GPIO26_ADC0)
unnamed: SW1.B, U1.32 (GPIO27_ADC1)
unnamed: SW1.S1, U1.34 (GPIO28_ADC2)
unnamed: U2.8 (GPIO_7), U3.3 (SCL)
unnamed: U2.10 (GPIO_8), U3.4 (SDA)
Row_0: D1.1 (K), D2.1 (K), D3.1 (K), D4.1 (K), D5.1 (K), D6.1 (K), D7.1 (K), D8.1 (K), D9.1 (K), D10.1 (K), D11.1 (K), D12.1 (K), D13.1 (K), D14.1 (K), D15.1 (K), D32.1 (K), U2.1 (GPIO_0)
Row_1: D16.1 (K), D17.1 (K), D18.1 (K), D19.1 (K), D20.1 (K), D21.1 (K), D22.1 (K), D23.1 (K), D24.1 (K), D25.1 (K), D26.1 (K), D27.1 (K), D28.1 (K), D29.1 (K), D30.1 (K), D31.1 (K), D33.1 (K), D34.1 (K), D35.1 (K), D36.1 (K), D57.1 (K), U2.2 (GPIO_1)
Row_2: D37.1 (K), D38.1 (K), D39.1 (K), D40.1 (K), D41.1 (K), D42.1 (K), D43.1 (K), D44.1 (K), D45.1 (K), D46.1 (K), D47.1 (K), D48.1 (K), D49.1 (K), D51.1 (K), D52.1 (K), D53.1 (K), D54.1 (K), D55.1 (K), D56.1 (K), U2.3 (GPIO_2)
Row_3: D50.1 (K), D58.1 (K), D59.1 (K), D60.1 (K), D61.1 (K), D62.1 (K), D63.1 (K), D64.1 (K), D65.1 (K), D66.1 (K), D67.1 (K), D68.1 (K), D69.1 (K), D70.1 (K), D71.1 (K), D72.1 (K), D73.1 (K), D91.1 (K), U2.4 (GPIO_3)
Row_4: D74.1 (K), D75.1 (K), D76.1 (K), D77.1 (K), D78.1 (K), D79.1 (K), D80.1 (K), D81.1 (K), D82.1 (K), D83.1 (K), D84.1 (K), D85.1 (K), D86.1 (K), D87.1 (K), D88.1 (K), D89.1 (K), D90.1 (K), U2.5 (GPIO_4)
Row_5: D92.1 (K), D93.1 (K), D94.1 (K), D95.1 (K), D96.1 (K), D97.1 (K), D98.1 (K), D99.1 (K), D100.1 (K), D101.1 (K), D102.1 (K), D103.1 (K), D104.1 (K), D105.1 (K), U2.6 (GPIO_5)

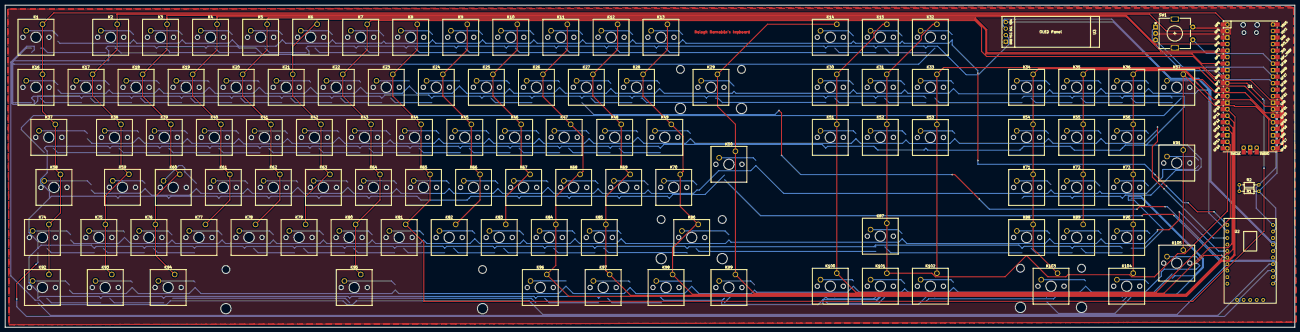
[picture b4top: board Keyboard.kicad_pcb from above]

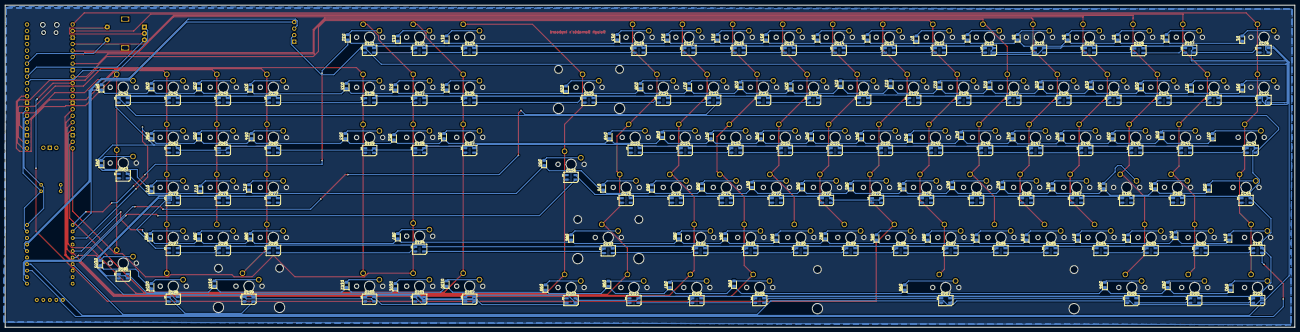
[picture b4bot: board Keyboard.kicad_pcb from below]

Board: 2 copper layers, 502.5 x 125.5 mm, 321 parts (210 on the bottom side), 245 nets.
